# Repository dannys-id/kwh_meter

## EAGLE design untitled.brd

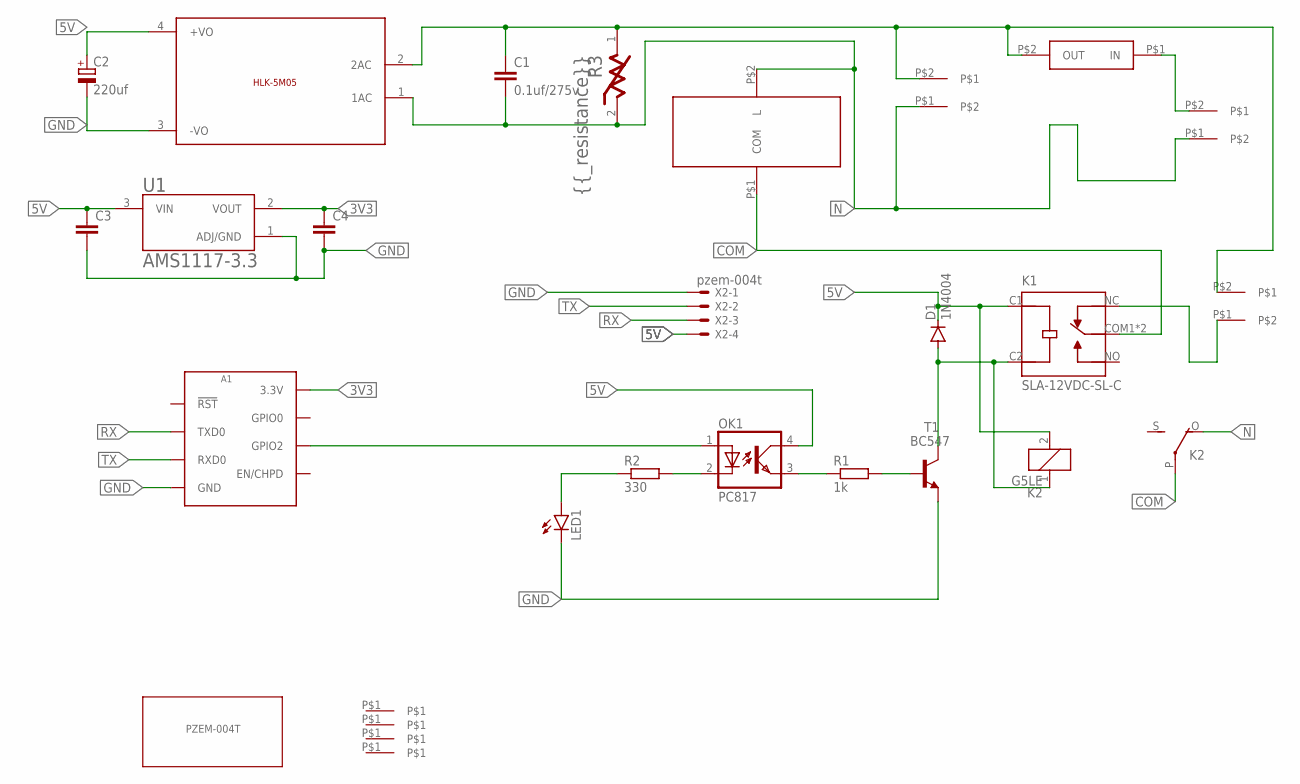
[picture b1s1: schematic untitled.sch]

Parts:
220: KF76
A1: ESP8266_ESP-01; ESP8266_ESP-01_NO-SILKSCREEN
C1: 0.1uf/275v; C7.5B5
C2: 220uf; E2-5
C3, C4: C-EUC0805; C0805
D1: 1N4004; DO41-10
K1: SLA-12VDC-SL-C; RELAY_SLA-12VDC-SL-C
K2: G5LE
LED1: LED5MM
OK1: PC817; DIL04
PZEM: KF76
R1: 1k; 0207/15
R2: 330; 0207/15
R3: 10D561K; BOURNS_INC_MOV-10D471K_0
RELAY: KF76
T1: BC547; TO92
U1: AMS1117-3.3; SOT229P700X180-4N
U$1: 5VDC/5W; HLK-5M05
U$2: TOROID
U$3: PZEM; PZEM_FOOTPRINT
U$4, U$5, U$6, U$7: SAPCER; SPACER
U$8: FUSE
X2: pzem-004t; 22-23-2041

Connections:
3V3: A1.3V3 (3.3V), C4.1, U1.2 (VOUT)
5V: C2.+, C3.1, D1.C, K1.C1 (COIL1), K2.2, OK1.4 (COL), U1.3 (VIN), U$1.4 (+VO), X2.4
COM: K1.COM1 (COM), K1.COM2 (COM), K2.P, U$2.P$1 (COM)
GND: A1.GND, C2.-, C3.2, C4.2, LED1.K (C), T1.1 (E), U1.1 (ADJ/GND), U$1.3 (-VO), X2.1
N: 220.P$1, C1.2, K2.O, PZEM.P$1, R3.2, U$1.1 (1AC), U$2.P$2 (L)
unnamed: OK1.3 (EMIT), R1.1
unnamed: R1.2, T1.2 (B)
unnamed: D1.A, K1.C2 (COIL2), K2.1, T1.3 (C)
unnamed: C1.1, PZEM.P$2, R3.1, RELAY.P$2, U$1.2 (2AC), U$8.P$2 (OUT)
unnamed: 220.P$2, U$8.P$1 (IN)
unnamed: K1.NC, RELAY.P$1
unnamed: LED1.A, R2.1
unnamed: OK1.2 (C), R2.2
unnamed: A1.GPIO2, OK1.1 (A)
RX: A1.TX (TXD0), X2.3
TX: A1.RX (RXD0), X2.2

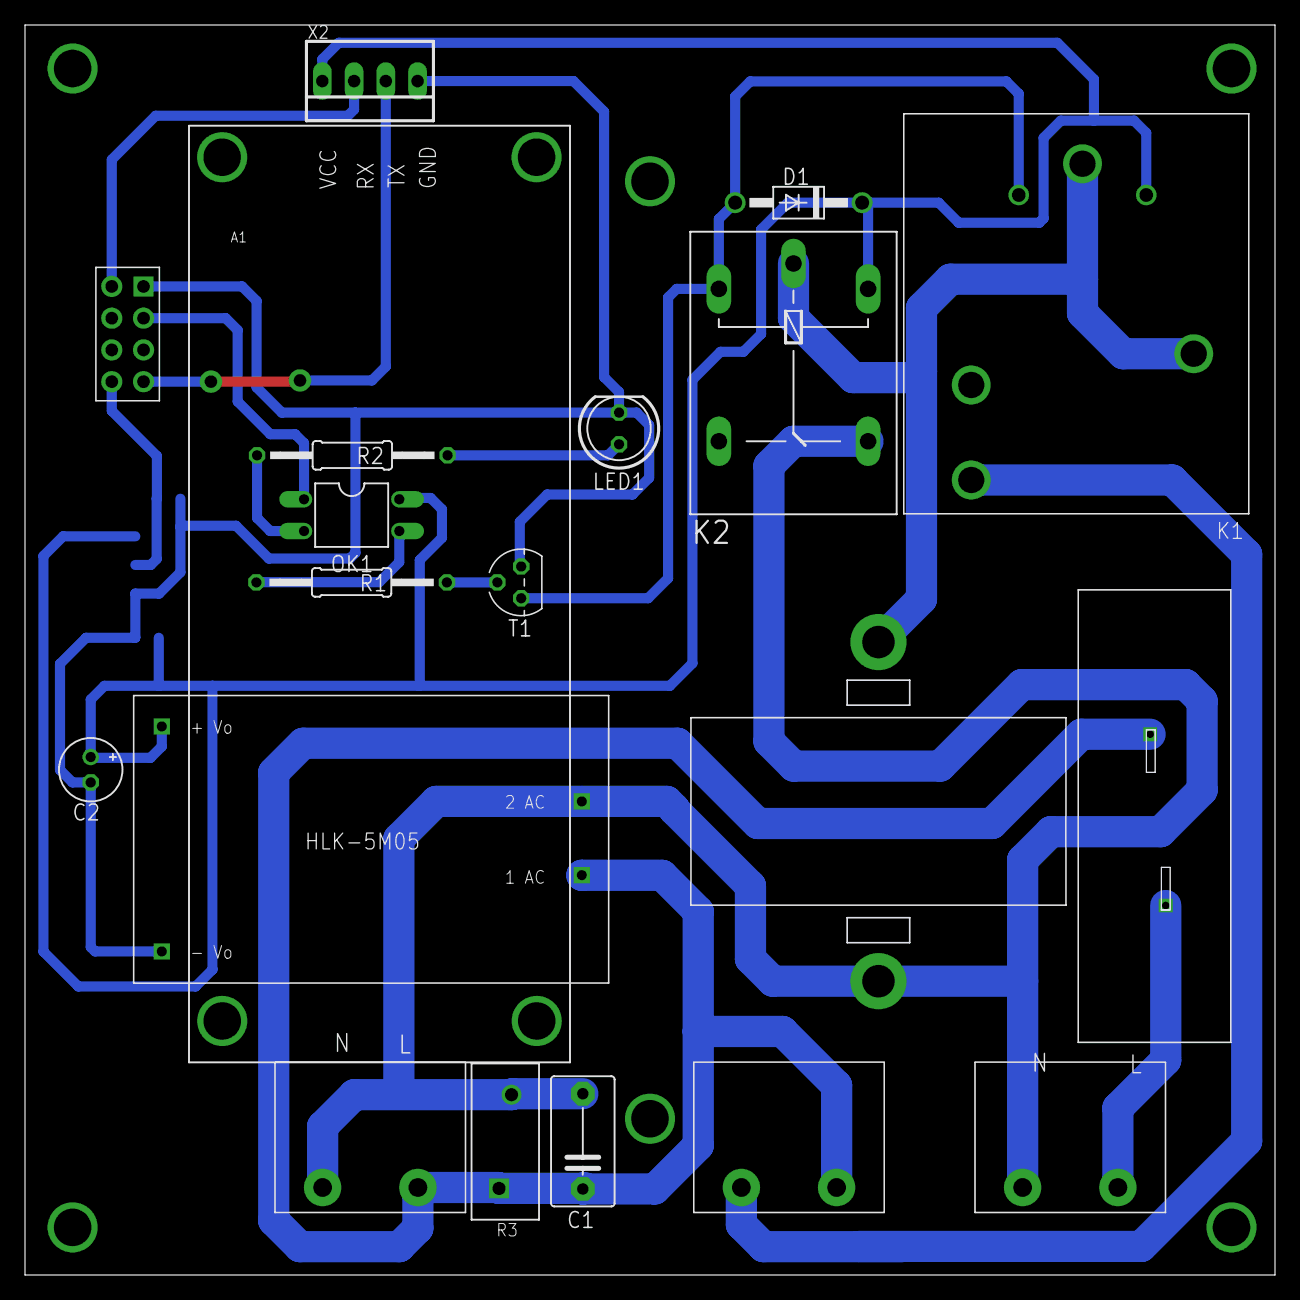
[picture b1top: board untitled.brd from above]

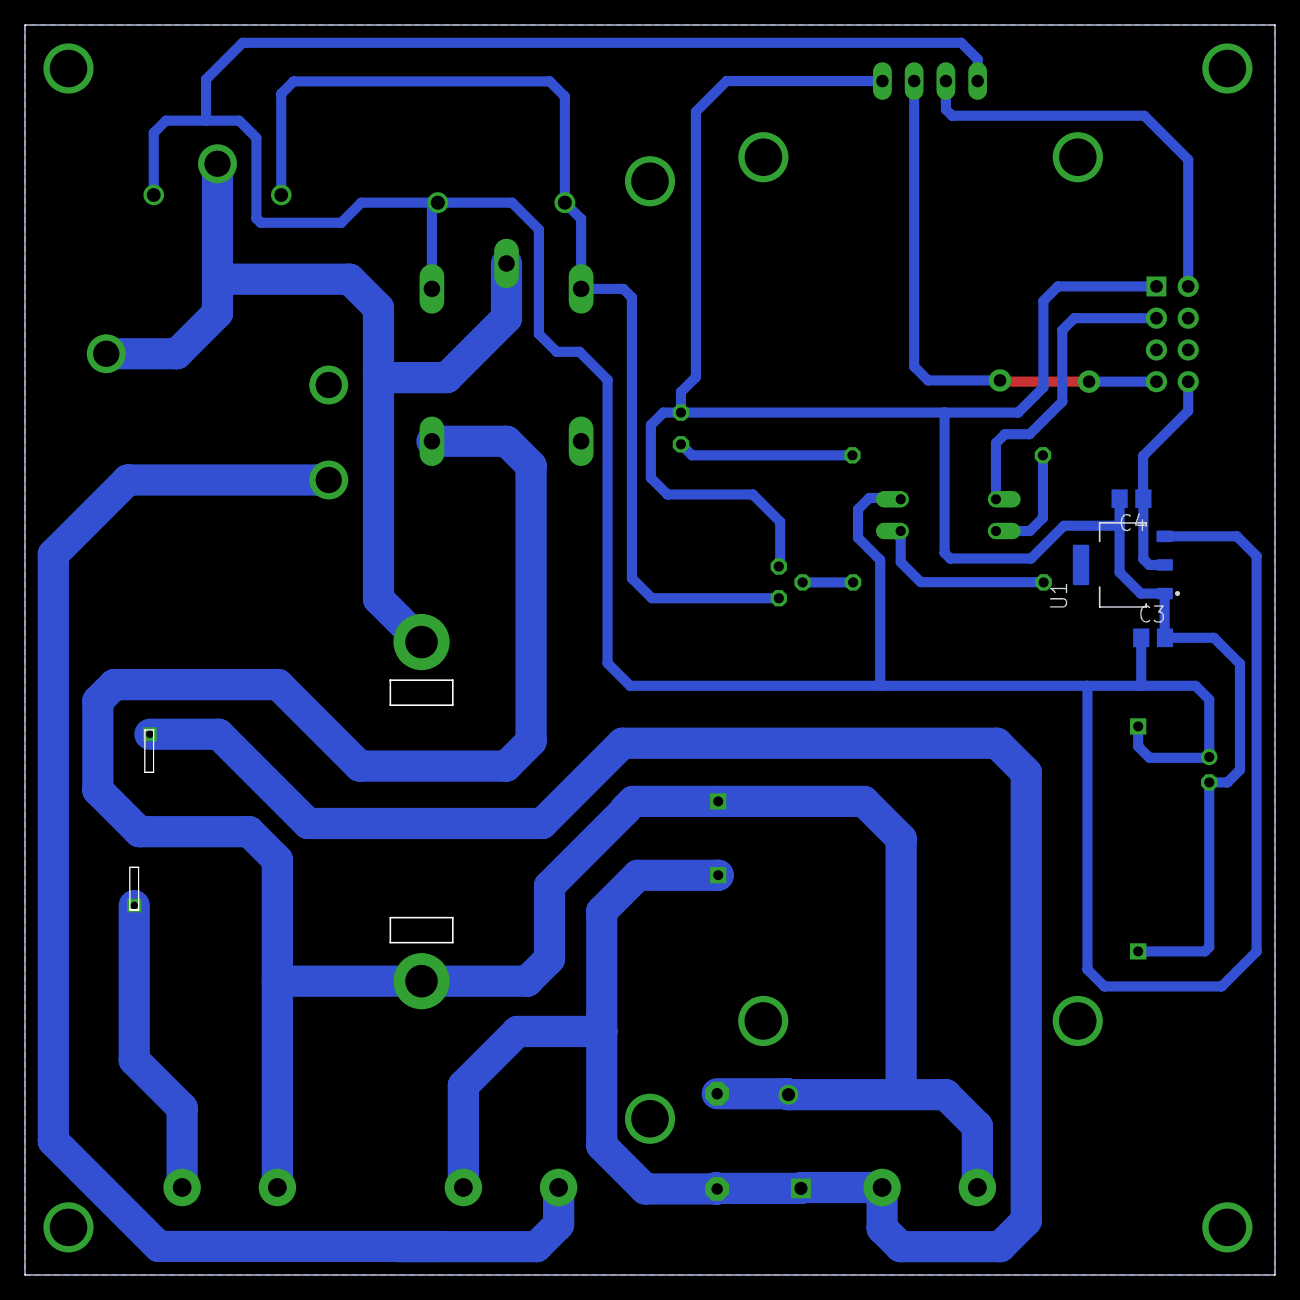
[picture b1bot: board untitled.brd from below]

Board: 2 copper layers, 99.9 x 99.9 mm, 27 parts (3 on the bottom side), 16 nets.

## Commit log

2022-09-11 Update untitled.b#1
2022-09-11 Update untitled.b#2
2022-09-11 Update untitled.b#3
2022-09-11 Update untitled.b#4
2022-09-11 Update untitled.b#5
2022-09-11 Update untitled.b#6
2022-09-11 Update untitled.b#7
2022-09-11 Update untitled.b#8
2022-09-11 Update untitled.b#9
